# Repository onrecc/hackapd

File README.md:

## Bill of Materials

| Reference | Qty | Value | Footprint | Datasheet | JLCPCB Link |
|-----------|-----|-------|-----------|-----------|-------------|
| D1, D2 | 2 | SK6812MINI | LED_SMD:LED_SK6812MINI_PLCC4_3.5x3.5mm_P1.75mm | [SK6812MINI Datasheet](https://cdn-shop.adafruit.com/product-files/2686/SK6812MINI_REV.01-1-2.pdf) | [C2886570](https://jlcpcb.com/partdetail/OpscoOptoelectronics-SK6812mini/C2886570) |
| SW1, SW2, SW3, SW4 | 4 | SW_Push | Button_Switch_Keyboard:SW_Cherry_MX_1.00u_PCB | ~ | [C5687012](https://api.jlcpcb.com/partdetail/CHERRY-MX1A11NN/C5687012) |
| SW5 | 1 | RotaryEncoder_Switch_MP | Rotary_Encoder:RotaryEncoder_Alps_EC11E-Switch_Vertical_H20mm | ~ | [C2687288](https://jlcpcb.com/partdetail/ALPSALPINE-EC11E1544407/C2687288) |
| U1 | 1 | XIAO-RP2040-DIP | OPL:XIAO-RP2040-DIP | | [C2040](https://jlcpcb.com/partdetail/RaspberryPi-RP2040/C2040) |

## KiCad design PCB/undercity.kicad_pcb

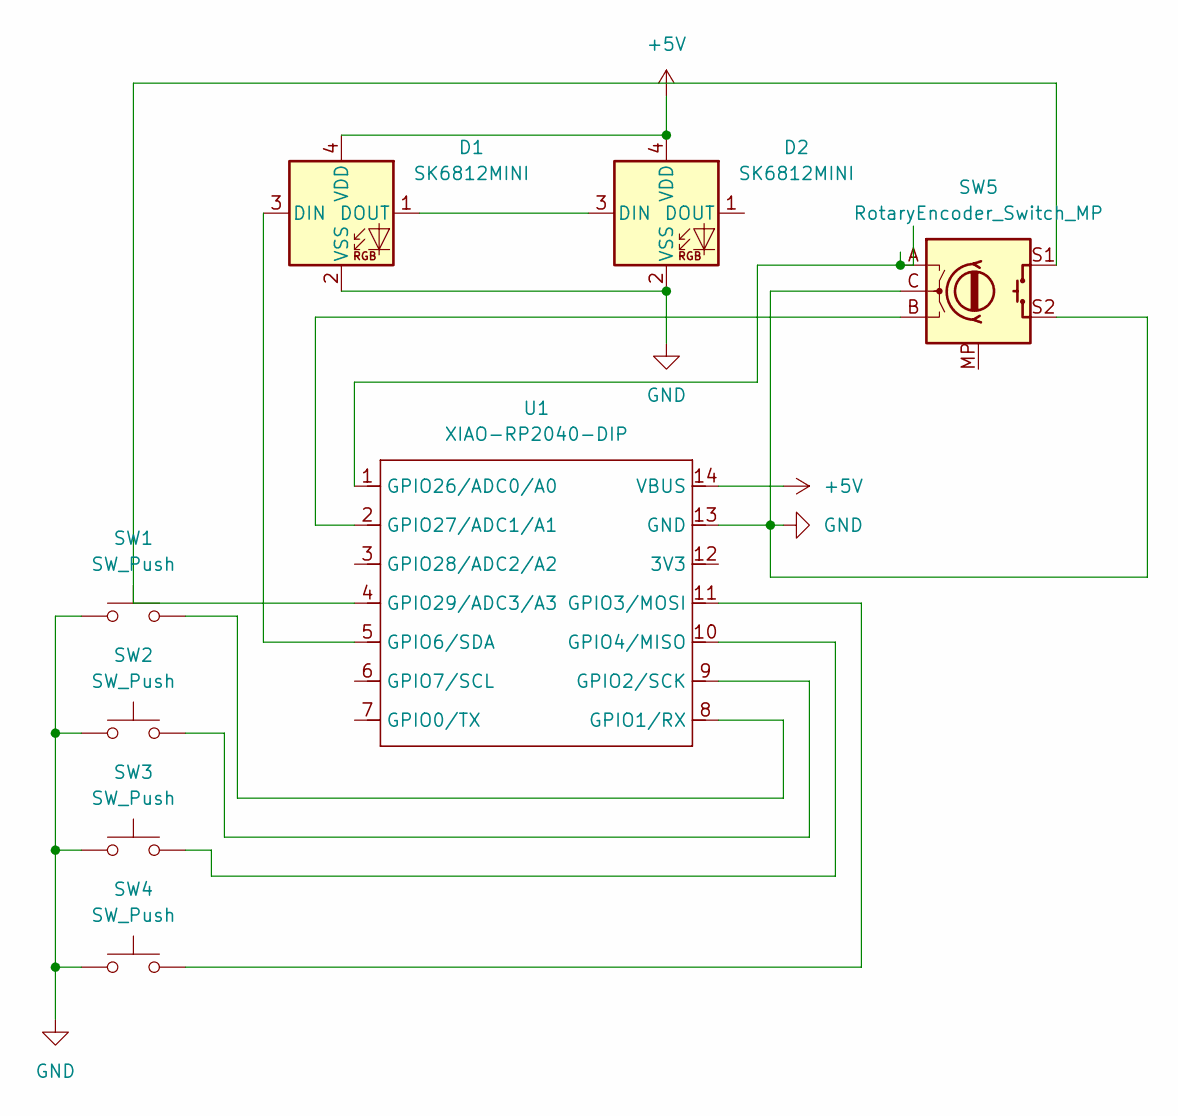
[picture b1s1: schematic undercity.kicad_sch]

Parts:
D1, D2: SK6812MINI; LED_SK6812MINI_PLCC4_3.5x3.5mm_P1.75mm
SW1, SW2, SW3, SW4: SW_Push; SW_Cherry_MX_1.00u_PCB
SW5: RotaryEncoder_Switch_MP; RotaryEncoder_Alps_EC11E-Switch_Vertical_H20mm
U1: XIAO-RP2040-DIP

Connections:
+5V: D1.4 (VDD), D2.4 (VDD), U1.14 (VBUS)
GND: D1.2 (VSS), D2.2 (VSS), SW1.1, SW2.1, SW3.1, SW4.1, SW5.C, SW5.S2, U1.13 (GND)
unnamed: D1.3 (DIN), U1.5 (GPIO6/SDA)
unnamed: D1.1 (DOUT), D2.3 (DIN)
unnamed: SW1.2, U1.8 (GPIO1/RX)
unnamed: SW2.2, U1.9 (GPIO2/SCK)
unnamed: SW4.2, U1.11 (GPIO3/MOSI)
unnamed: SW3.2, U1.10 (GPIO4/MISO)
unnamed: SW5.A, U1.1 (GPIO26/ADC0/A0)
unnamed: SW5.B, U1.2 (GPIO27/ADC1/A1)
unnamed: SW5.S1, U1.4 (GPIO29/ADC3/A3)

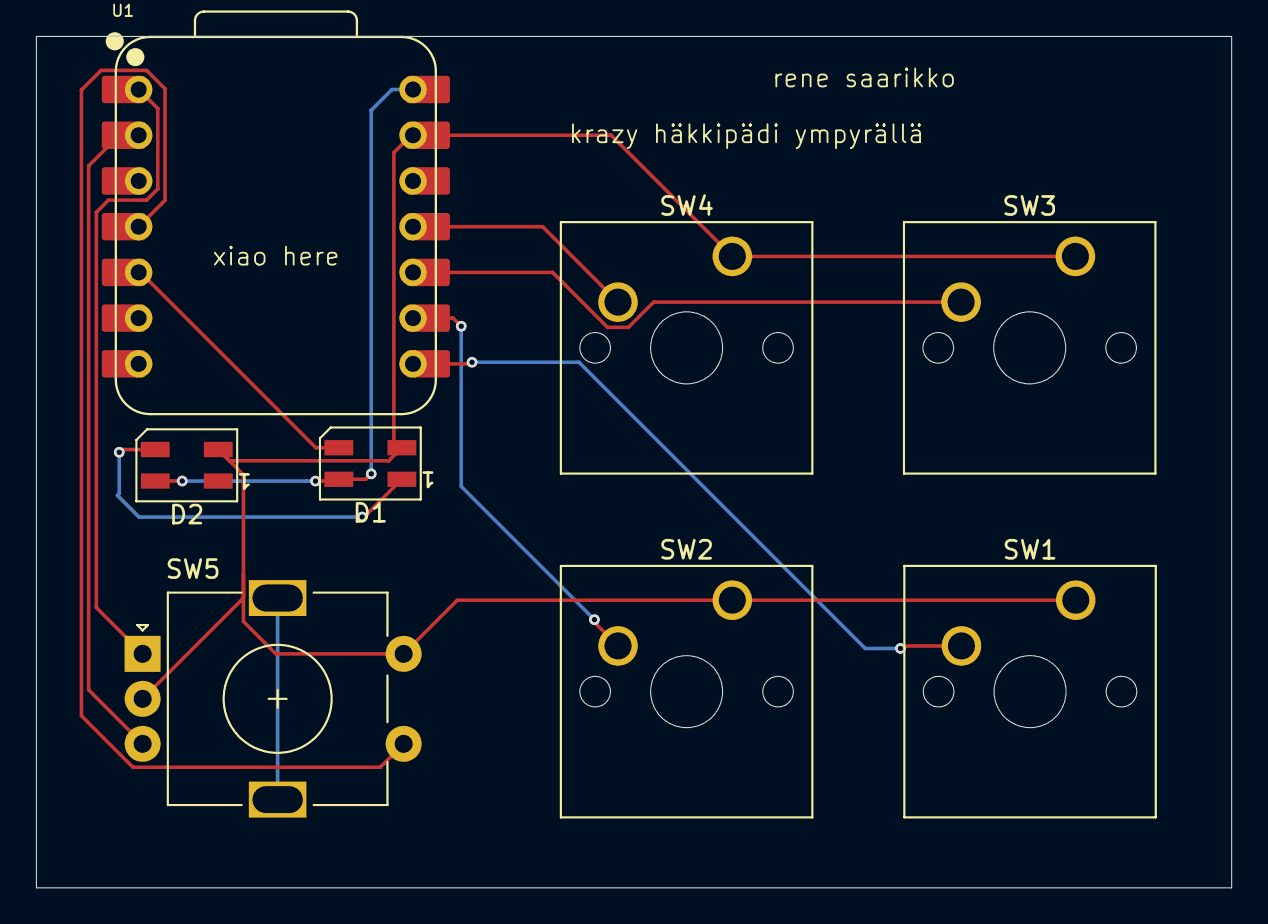
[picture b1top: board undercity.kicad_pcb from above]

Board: 2 copper layers, 66.4 x 47.3 mm, 8 parts (0 on the bottom side), 11 nets.

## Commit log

2025-07-11 bom and 3d model
2025-07-11 Initial plan
2025-07-11 Add JLCPCB_Link column to undercity.csv with assembly catalog URLs
2025-07-11 Add JLCPCB_Link column to undercity.csv with component links
2025-07-11 whole project
2025-07-11 hackpad commit
